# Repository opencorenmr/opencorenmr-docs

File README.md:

## Licensing Terms

- content under `./hardware` is licensed under `CERN-OHL-W-2.0` (see [LICENSE-for-hardware](https://github.com/moedn/opencorenmr-docs/blob/master/LICENSE-for-hardware))
- everything else is licensed under `MIT` (see [LICENSE](LICENSE))

---

## Welcome to GitHub Pages

You can use the [editor on GitHub](https://github.com/opencorenmr/opencorenmr.github.io/edit/master/README.md) to maintain and preview the content for your website in Markdown files.

Whenever you commit to this repository, GitHub Pages will run [Jekyll](https://jekyllrb.com/) to rebuild the pages in your site, from the content in your Markdown files.

### Markdown

Markdown is a lightweight and easy-to-use syntax for styling your writing. It includes conventions for

```markdown
Syntax highlighted code block

# Header 1
## Header 2
### Header 3

- Bulleted
- List

1. Numbered
2. List

**Bold** and _Italic_ and `Code` text

[Link](url) and 
```

For more details see [GitHub Flavored Markdown](https://guides.github.com/features/mastering-markdown/).

### Jekyll Themes

Your Pages site will use the layout and styles from the Jekyll theme you have selected in your [repository settings](https://github.com/opencorenmr/opencorenmr.github.io/settings). The name of this theme is saved in the Jekyll `_config.yml` configuration file.

### Support or Contact

Having trouble with Pages? Check out our [documentation](https://help.github.com/categories/github-pages-basics/) or [contact support](https://github.com/contact) and we’ll help you sort it out.

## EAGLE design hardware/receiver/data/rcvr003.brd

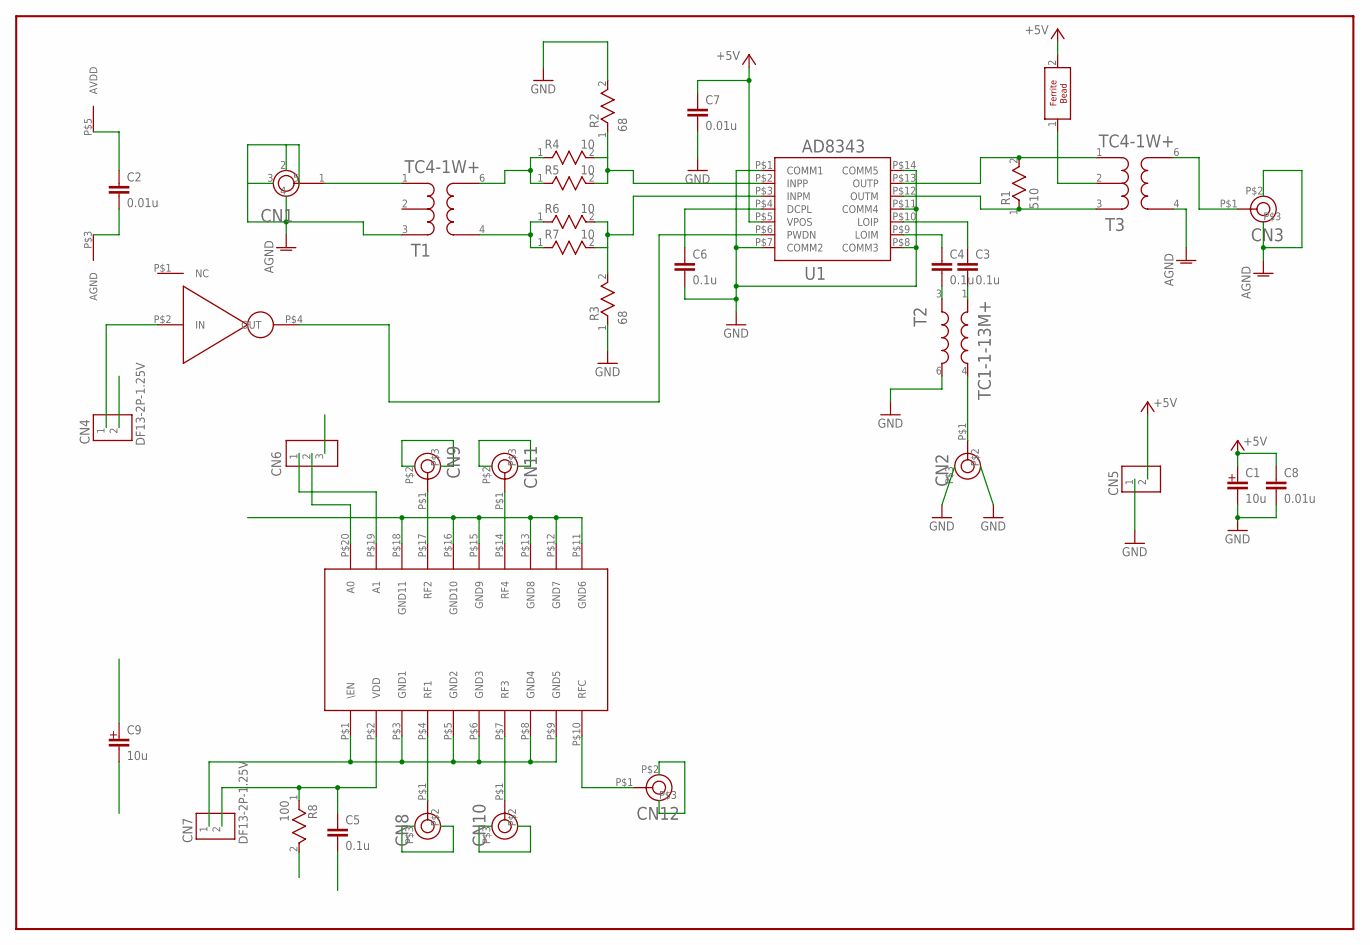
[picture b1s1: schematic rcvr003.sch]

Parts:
C1, C9: 10u; 3216_POLAR
C2, C7: 0.01u; 1005
C3, C4, C5, C6: 0.1u; 1005
C8: 0.01u; 1608
CN1: SMASTRAIGHT; SMA_STRAIGHT
CN2, CN3, CN8, CN9, CN10, CN11, CN12: U.FL-R-SMT
CN4, CN5, CN7: DF13-2P-1.25V; DF13-2P-12.5V
CN6: DF13-3P-1.25V
FB2: FERRITEBEAD; 1608
R1: 510; 1608
R2, R3: 68; 1608
R4, R5, R6, R7: 10; 1005
R8: 100; 1608
T1, T3: TC4-1W+; AT224
T2: TC1-1-13M+; AT224
U1: AD8343
U2: MC74VHC1G04
U3: ADG904; ADG904_TSSOP

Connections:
3.3V: C5.1, C9.1, CN7.2, R8.1, U3.P$2 (VDD)
+5V: C1.1, C2.1, C7.1, C8.1, CN5.2, FB2.2, U1.P$5 (VPOS), U2.P$5 (AVDD)
AGND: C1.2, C2.2, C6.2, C7.2, C8.2, CN1.2 (GND), CN1.3 (GND), CN1.4 (GND), CN1.5 (GND), CN2.P$2 (AGND), CN2.P$3 (AGND2), CN3.P$2 (AGND), CN3.P$3 (AGND2), CN4.2, CN5.1, R2.2, R3.1, T1.3, T2.6 (4), T3.4, U1.P$1 (COMM1), U1.P$7 (COMM2), U1.P$8 (COMM3), U1.P$11 (COMM4), U1.P$14 (COMM5), U2.P$3 (AGND)
GND2: C5.2, C9.2, CN7.1, CN8.P$2 (AGND), CN8.P$3 (AGND2), CN9.P$2 (AGND), CN9.P$3 (AGND2), CN10.P$2 (AGND), CN10.P$3 (AGND2), CN11.P$2 (AGND), CN11.P$3 (AGND2), CN12.P$2 (AGND), CN12.P$3 (AGND2), U3.P$1 (\EN), U3.P$3 (GND1), U3.P$5 (GND2), U3.P$6 (GND3), U3.P$8 (GND4), U3.P$9 (GND5), U3.P$11 (GND6), U3.P$12 (GND7), U3.P$13 (GND8), U3.P$15 (GND9), U3.P$16 (GND10), U3.P$18 (GND11)
N2: R8.2
unnamed: CN4.1, U2.P$2 (IN)
unnamed: CN12.P$1, U3.P$10 (RFC)
unnamed: CN10.P$1, U3.P$7 (RF3)
unnamed: CN8.P$1, U3.P$4 (RF1)
unnamed: CN9.P$1, U3.P$17 (RF2)
unnamed: CN11.P$1, U3.P$14 (RF4)
unnamed: CN6.2, U3.P$20 (A0)
unnamed: CN2.P$1, T2.4 (3)
unnamed: CN1.1, T1.1
unnamed: U1.P$6 (PWDN), U2.P$4 (OUT)
unnamed: CN6.1, U3.P$19 (A1)
unnamed: CN3.P$1, T3.6
unnamed: FB2.1, T3.2
unnamed: R1.2, T3.1, U1.P$13 (OUTP)
unnamed: R1.1, T3.3, U1.P$12 (OUTM)
unnamed: C6.1, U1.P$4 (DCPL)
unnamed: C4.1, U1.P$9 (LOIM)
unnamed: C3.1, U1.P$10 (LOIP)
unnamed: C4.2, T2.3 (2)
unnamed: C3.2, T2.1
unnamed: R2.1, R4.2, R5.2, U1.P$2 (INPP)
unnamed: R3.2, R6.2, R7.2, U1.P$3 (INPM)
unnamed: R4.1, R5.1, T1.6
unnamed: R6.1, R7.1, T1.4

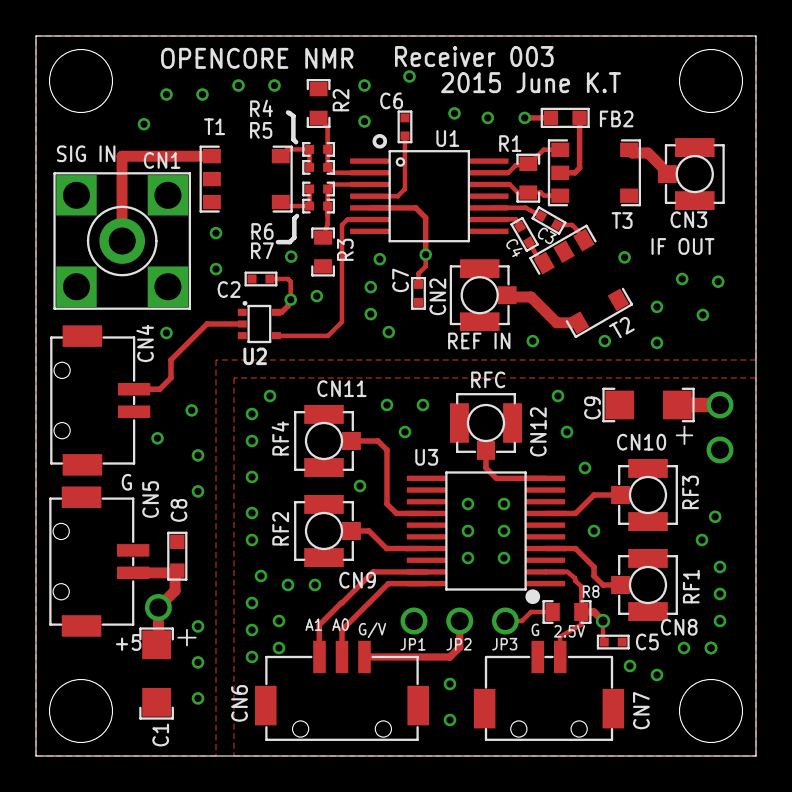
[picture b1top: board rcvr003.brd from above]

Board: 4 copper layers, 40.0 x 40.0 mm, 36 parts (0 on the bottom side), 28 nets.

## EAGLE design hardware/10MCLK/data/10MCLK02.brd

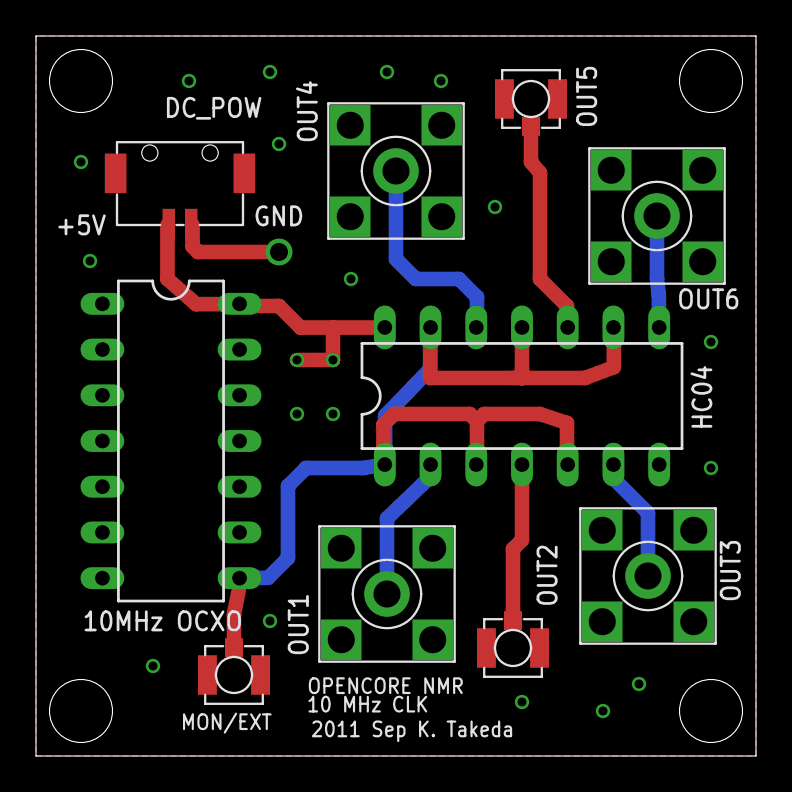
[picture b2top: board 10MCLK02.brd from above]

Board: 2 copper layers, 40.0 x 40.0 mm, 10 parts (0 on the bottom side), 9 nets.

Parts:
10MCLK: DIL14
DC_POW: DF13-2P-12.5V
E$2: DIL14
E$10, E$11: U.FL-R-SMT
MON/EXT: U.FL-R-SMT
OUT1, OUT3, OUT4, OUT6: SMA_STRAIGHT

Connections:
10IN: 10MCLK.8, E$2.1, E$2.3, E$2.5, E$2.9, E$2.11, E$2.13, MON/EXT.P$1
+5V: 10MCLK.14, DC_POW.2, E$2.14
GND: 10MCLK.7, DC_POW.1, E$2.7, E$10.P$2, E$10.P$3, E$11.P$2, E$11.P$3, MON/EXT.P$2, MON/EXT.P$3, OUT1.2, OUT1.3, OUT1.4, OUT1.5, OUT3.2, OUT3.3, OUT3.4, OUT3.5, OUT4.2, OUT4.3, OUT4.4, OUT4.5, OUT6.2, OUT6.3, OUT6.4, OUT6.5
S$2: E$2.4, E$10.P$1
S$5: E$2.10, E$11.P$1
S$7: E$2.12, OUT4.1
S$8: E$2.8, OUT6.1
S$9: E$2.2, OUT1.1
S$10: E$2.6, OUT3.1

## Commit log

2018-04-27 Set theme jekyll-theme-cayman
2018-04-27 commit by Takeda
2018-05-21 gpibOnLinux.md created
2018-06-18 linux appimage added
2018-06-18 screenshot added
2018-06-19 commit by Takeda
    bug fixed (save ascii data)
2018-07-04 Create temporary
2018-07-04 Create temp
2018-07-21 commit by Takeda
    on-line and off-line exp settings
2018-08-28 minor corrections
2018-09-03 MProg screenshots
2018-09-03 opencore-usb.ept uploaded
2018-09-03 u.png uploaded
2018-09-03 EPROM (usb)
2018-09-03 wrong path to "usb_eprom" fixed
2018-09-04 back to index added
2019-01-09 Grammar error corrected.
2019-01-11 driver setup
2019-01-11 link correction
2019-01-11 link correction again
2019-01-28 Commit by Takeda on a local computer
2019-01-28 Commit by Takeda on a local computer
    garbage file removed
2019-02-05 correction ```cpp -> ```
2019-02-06 commit from ipad
2019-05-07 Typo errors in opencoreNMR.rules was corrected.
    ACTION=="add" was corrected to ACTION=="add"
2020-02-13 Update dds2.md
    Typo error (binary number) in "Setting the frequency-sweep rate" has been corrected
2023-04-28 add license
2023-04-28 add license for hardware
2023-04-28 add a note on licensing terms
2023-05-10 Update DDS2.md
    link typo error corrected
    (data/DDS2-03.brd)
2023-05-10 Update receiver.md
    Link to "solder side silkscreen" was deleted (because the data did not exist from the beginning!)
2026-02-06 ppg-new2026feb.md
2026-02-09 lapack update
